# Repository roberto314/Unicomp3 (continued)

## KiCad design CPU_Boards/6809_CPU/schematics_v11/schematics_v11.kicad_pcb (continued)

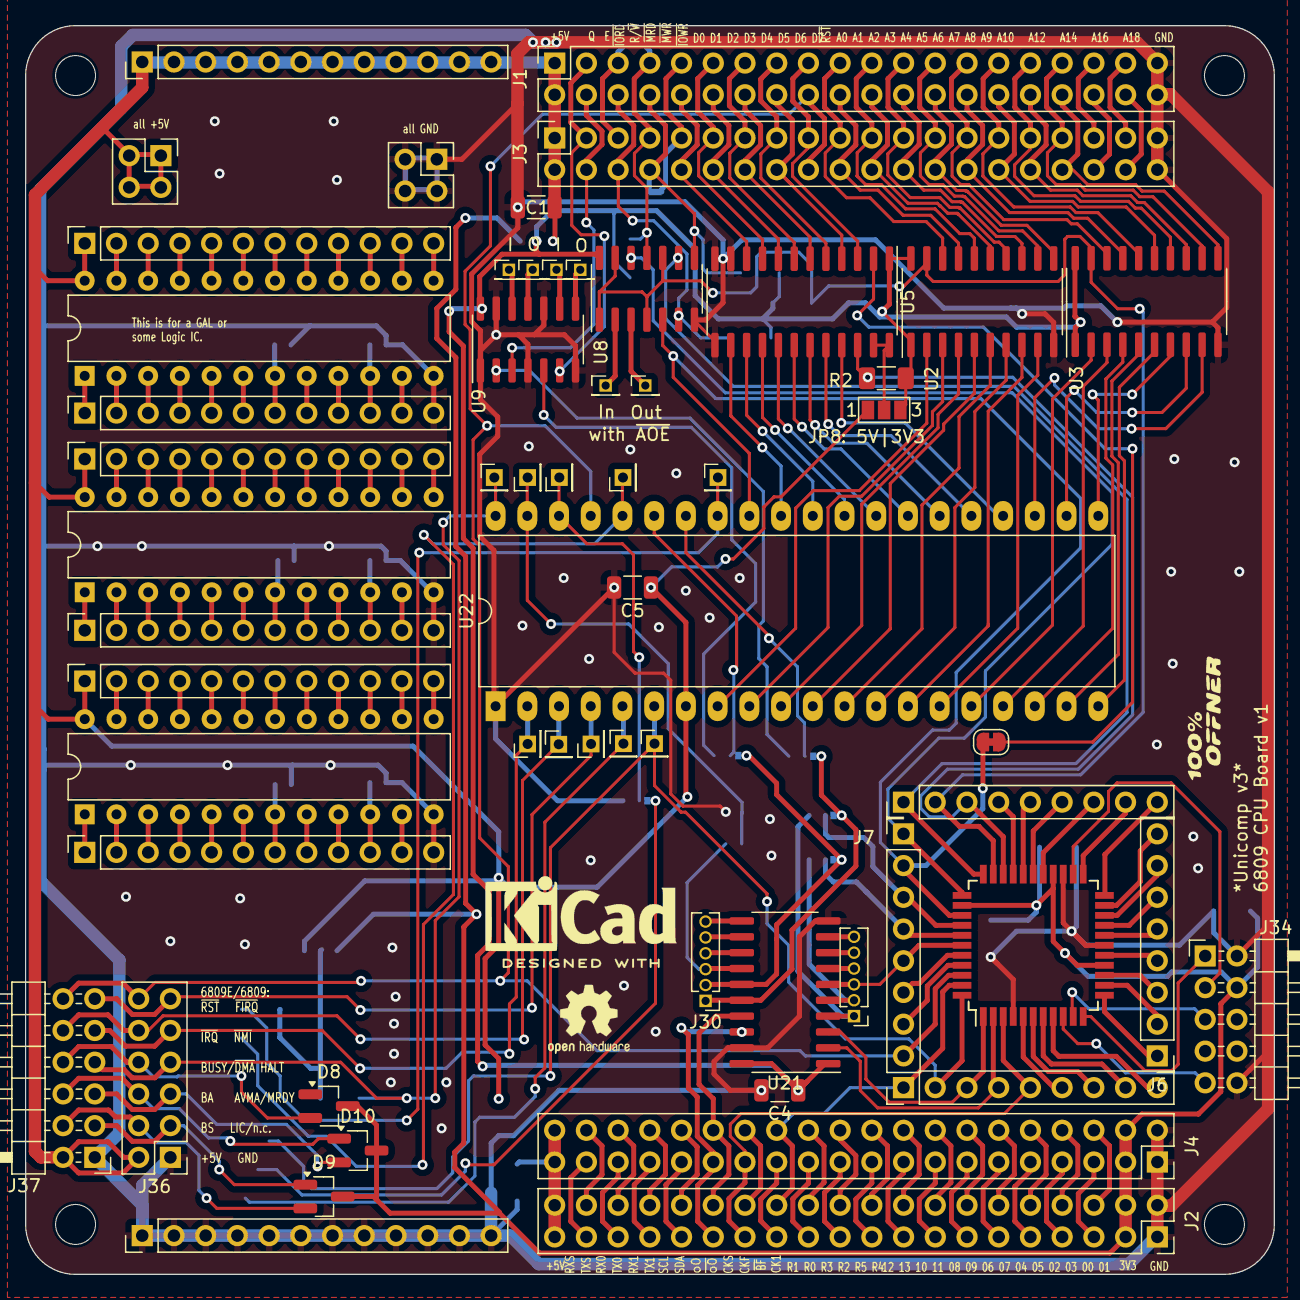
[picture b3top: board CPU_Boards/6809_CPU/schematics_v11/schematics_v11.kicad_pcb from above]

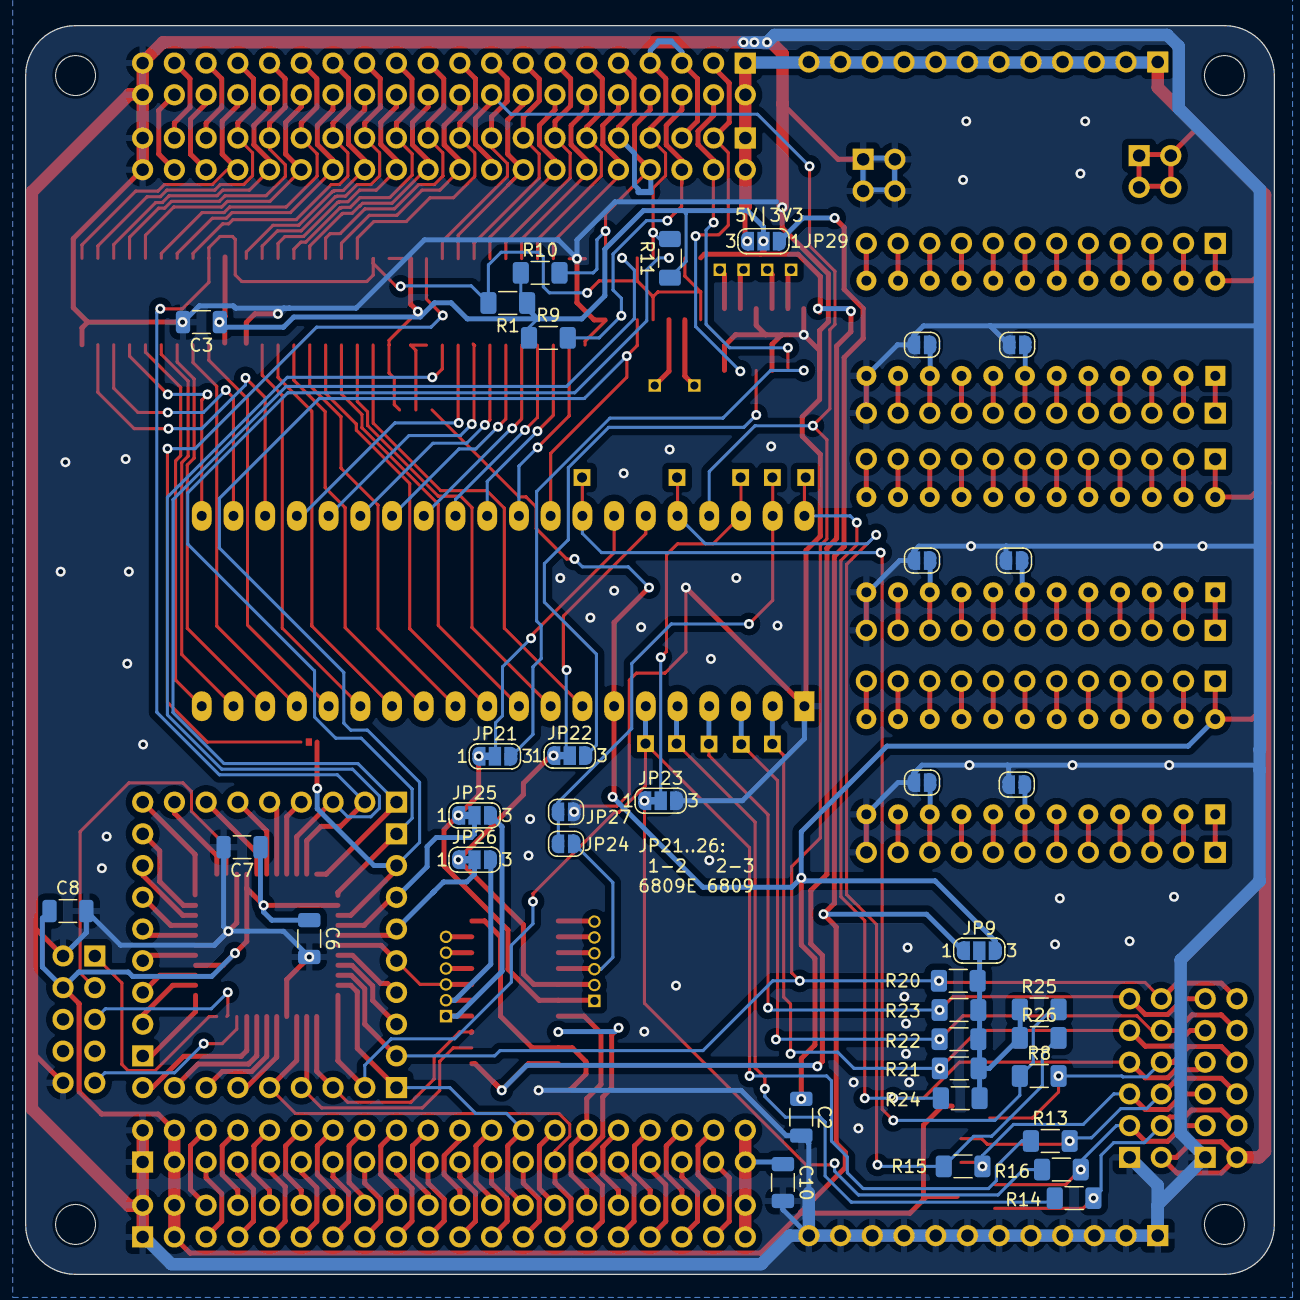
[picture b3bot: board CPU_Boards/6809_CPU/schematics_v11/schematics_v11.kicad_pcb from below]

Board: 2 copper layers, 100.0 x 100.0 mm, 105 parts (39 on the bottom side), 239 nets.

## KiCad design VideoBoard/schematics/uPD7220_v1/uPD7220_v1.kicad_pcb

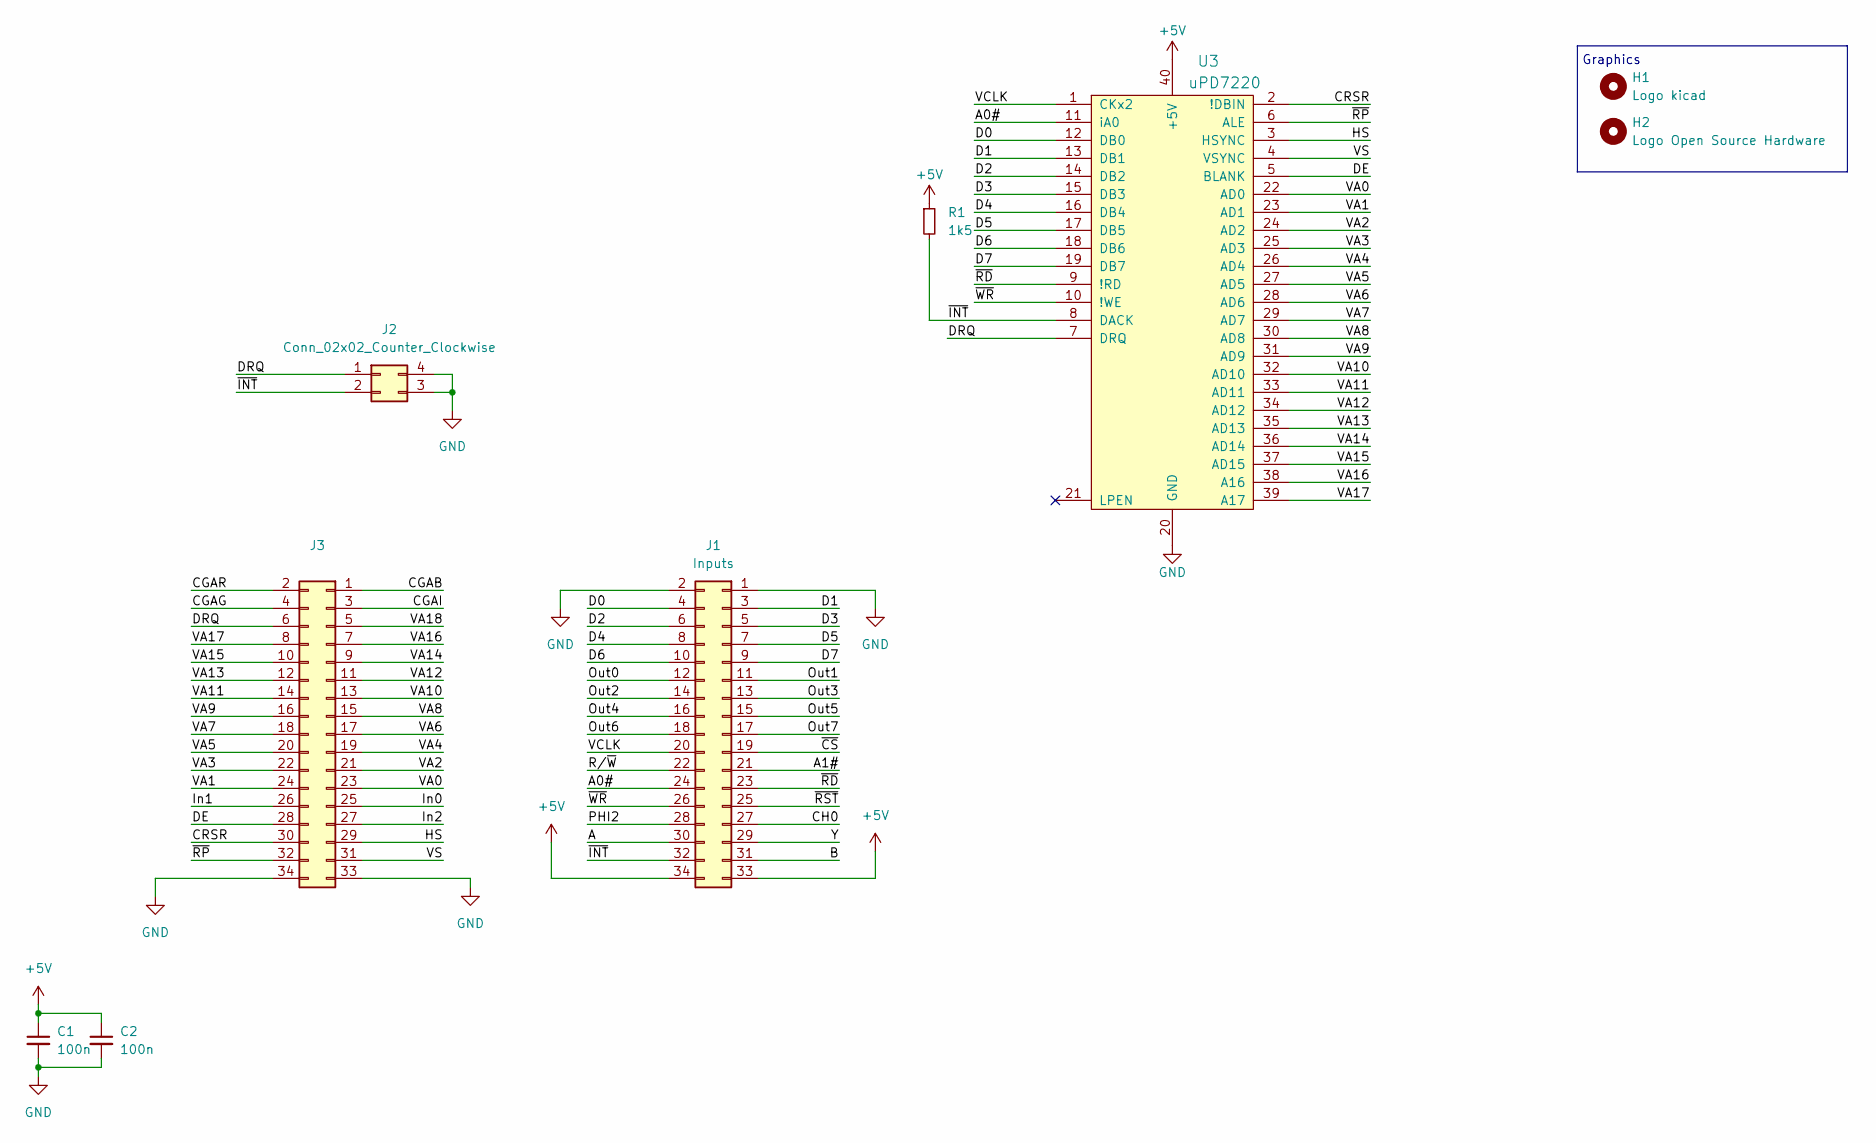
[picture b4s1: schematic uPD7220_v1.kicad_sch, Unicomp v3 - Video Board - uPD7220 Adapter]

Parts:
C1, C2: 100n; C_1206_3216Metric_Pad1.33x1.80mm_HandSolder
H1: Logo kicad; KiCad-Logo2_6mm_SilkScreen
H2: Logo Open Source Hardware; OSHW-Logo2_7.3x6mm_SilkScreen
J1: Inputs; PinHeader_2x17_P2.54mm_Vertical
J2: Conn_02x02_Counter_Clockwise; PinHeader_2x02_P2.54mm_Horizontal
J3: Outputs; PinHeader_2x17_P2.54mm_Vertical
R1: 1k5; R_1206_3216Metric_Pad1.30x1.75mm_HandSolder
U3: uPD7220; DIP-40_W15.24mm_Socket

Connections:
+5V: C1.1, C2.1, J1.33, J1.34, R1.1, U3.40 (+5V)
/A: J1.30
/A0#: J1.24, U3.11 (iA0)
/A1#: J1.21
/B: J1.31
/CGAB: J3.1
/CGAG: J3.4
/CGAI: J3.3
/CGAR: J3.2
/CH0: J1.27
/CRSR: J3.30, U3.2 (!DBIN)
/D0: J1.4, U3.12 (DB0)
/D1: J1.3, U3.13 (DB1)
/D2: J1.6, U3.14 (DB2)
/D3: J1.5, U3.15 (DB3)
/D4: J1.8, U3.16 (DB4)
/D5: J1.7, U3.17 (DB5)
/D6: J1.10, U3.18 (DB6)
/D7: J1.9, U3.19 (DB7)
/DE: J3.28, U3.5 (BLANK)
/DRQ: J2.1, J3.6, U3.7 (DRQ)
/HS: J3.29, U3.3 (HSYNC)
/In0: J3.25
/In1: J3.26
/In2: J3.27
/Out0: J1.12
/Out1: J1.11
/Out2: J1.14
/Out3: J1.13
/Out4: J1.16
/Out5: J1.15
/Out6: J1.18
/Out7: J1.17
/PHI2: J1.28
/R/~W: J1.22
/VA0: J3.23, U3.22 (AD0)
/VA1: J3.24, U3.23 (AD1)
/VA2: J3.21, U3.24 (AD2)
/VA3: J3.22, U3.25 (AD3)
/VA4: J3.19, U3.26 (AD4)
/VA5: J3.20, U3.27 (AD5)
/VA6: J3.17, U3.28 (AD6)
/VA7: J3.18, U3.29 (AD7)
/VA8: J3.15, U3.30 (AD8)
/VA9: J3.16, U3.31 (AD9)
/VA10: J3.13, U3.32 (AD10)
/VA11: J3.14, U3.33 (AD11)
/VA12: J3.11, U3.34 (AD12)
/VA13: J3.12, U3.35 (AD13)
/VA14: J3.9, U3.36 (AD14)
/VA15: J3.10, U3.37 (AD15)
/VA16: J3.7, U3.38 (A16)
/VA17: J3.8, U3.39 (A17)
/VA18: J3.5
/VCLK: J1.20, U3.1 (CKx2)
/VS: J3.31, U3.4 (VSYNC)
/Y: J1.29
/~CS: J1.19
/~INT: J1.32, J2.2, R1.2, U3.8 (DACK)
/~RD: J1.23, U3.9 (!RD)
/~RP: J3.32, U3.6 (ALE)
/~RST: J1.25
/~WR: J1.26, U3.10 (!WE)
GND: C1.2, C2.2, J1.1, J1.2, J2.3, J2.4, J3.33, J3.34, U3.20 (GND)

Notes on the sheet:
Graphics

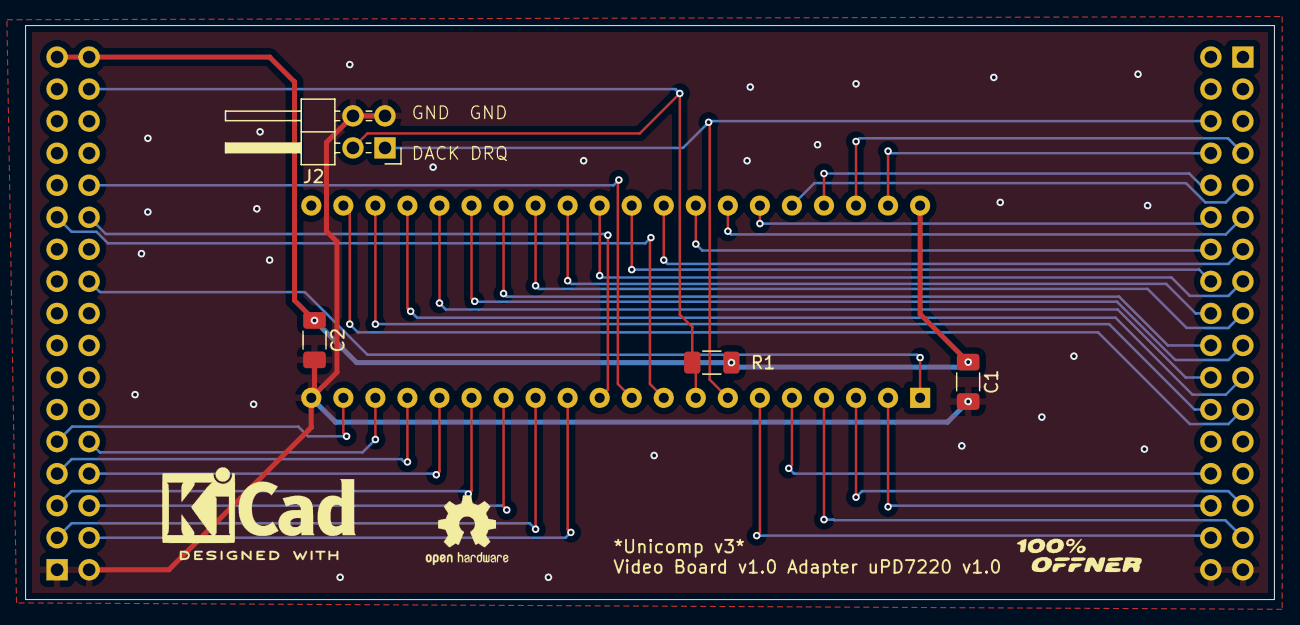
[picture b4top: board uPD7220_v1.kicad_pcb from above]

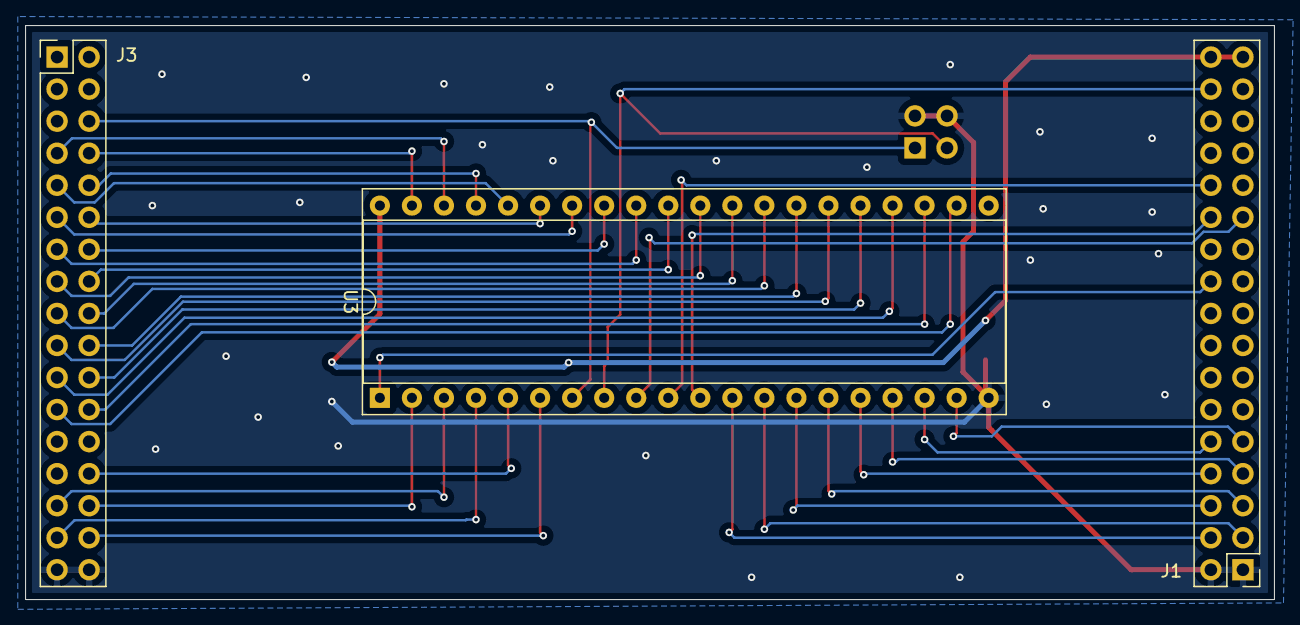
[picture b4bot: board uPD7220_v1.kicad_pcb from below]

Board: 2 copper layers, 99.0 x 45.5 mm, 9 parts (3 on the bottom side), 39 nets.

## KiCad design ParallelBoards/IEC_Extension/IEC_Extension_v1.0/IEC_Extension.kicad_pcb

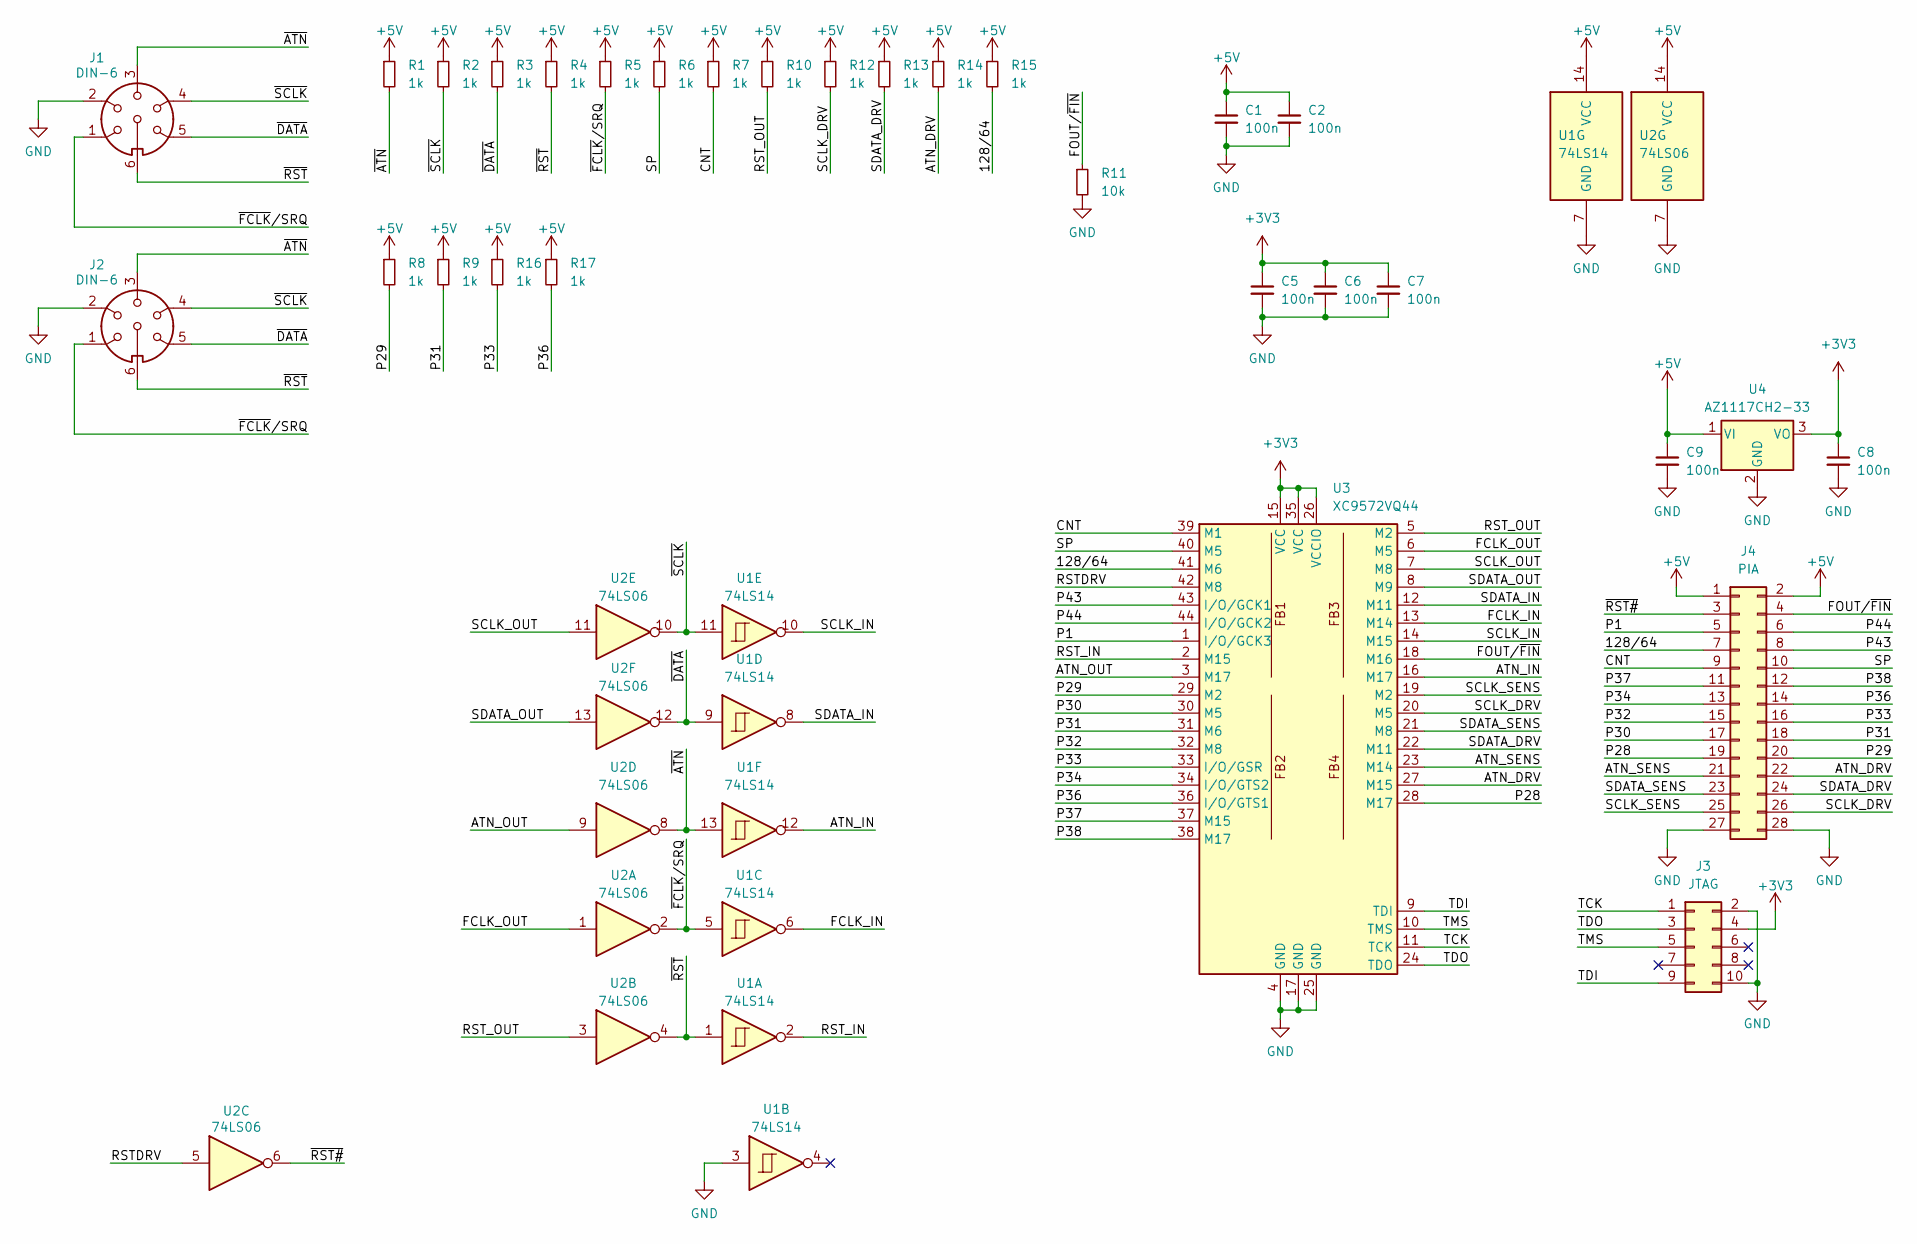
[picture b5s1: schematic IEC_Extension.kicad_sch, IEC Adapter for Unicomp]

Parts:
C1, C2, C5, C6, C7, C8, C9: 100n; C_1206_3216Metric_Pad1.33x1.80mm_HandSolder
J1, J2: DIN-6; C64_IEC
J3: JTAG; PinHeader_2x05_P2.54mm_Horizontal
J4: PIA; PinHeader_2x14_P2.54mm_Vertical
R1, R2, R3, R4, R5, R6, R7, R8, R9, R10, R12, R13, R14, R15, R16, R17: 1k; R_1206_3216Metric_Pad1.30x1.75mm_HandSolder
R11: 10k; R_1206_3216Metric_Pad1.30x1.75mm_HandSolder
U1: 74LS14; SOIC-14_3.9x8.7mm_P1.27mm
U2: 74LS06; SOIC-14_3.9x8.7mm_P1.27mm
U3: XC9572VQ44; TQFP-44_10x10mm_P0.8mm
U4: AZ1117CH2-33; SOT-223-3_TabPin2

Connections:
+3V3: C5.1, C6.1, C7.1, C8.1, J3.4, U3.15 (VCC), U3.26 (VCCIO), U3.35 (VCC), U4.3 (VO)
+5V: C1.1, C2.1, C9.1, J4.1, J4.2, R1.1, R2.1, R3.1, R4.1, R5.1, R6.1, R7.1, R8.1, R9.1, R10.1, R12.1, R13.1, R14.1, R15.1, R16.1, R17.1, U1.14 (VCC), U2.14 (VCC), U4.1 (VI)
/128/64: J4.7, R15.2, U3.41 (M6)
/ATN_DRV: J4.22, R14.2, U3.27 (M15)
/ATN_IN: U1.12, U3.16 (M17)
/ATN_OUT: U2.9, U3.3 (M17)
/ATN_SENS: J4.21, U3.23 (M14)
/CNT: J4.9, R7.2, U3.39 (M1)
/FCLK_IN: U1.6, U3.13 (M14)
/FCLK_OUT: U2.1, U3.6 (M5)
/FOUT/~FIN: J4.4, R11.1, U3.18 (M16)
/P1: J4.5, U3.1 (I/O/GCK3)
/P28: J4.19, U3.28 (M17)
/P29: J4.20, R8.2, U3.29 (M2)
/P30: J4.17, U3.30 (M5)
/P31: J4.18, R9.2, U3.31 (M6)
/P32: J4.15, U3.32 (M8)
/P33: J4.16, R16.2, U3.33 (I/O/GSR)
/P34: J4.13, U3.34 (I/O/GTS2)
/P36: J4.14, R17.2, U3.36 (I/O/GTS1)
/P37: J4.11, U3.37 (M15)
/P38: J4.12, U3.38 (M17)
/P43: J4.8, U3.43 (I/O/GCK1)
/P44: J4.6, U3.44 (I/O/GCK2)
/RSTDRV: U2.5, U3.42 (M8)
/RST_IN: U1.2, U3.2 (M15)
/RST_OUT: R10.2, U2.3, U3.5 (M2)
/SCLK_DRV: J4.26, R12.2, U3.20 (M5)
/SCLK_IN: U1.10, U3.14 (M15)
/SCLK_OUT: U2.11, U3.7 (M8)
/SCLK_SENS: J4.25, U3.19 (M2)
/SDATA_DRV: J4.24, R13.2, U3.22 (M11)
/SDATA_IN: U1.8, U3.12 (M11)
/SDATA_OUT: U2.13, U3.8 (M9)
/SDATA_SENS: J4.23, U3.21 (M8)
/SP: J4.10, R6.2, U3.40 (M5)
/TCK: J3.1, U3.11 (TCK)
/TDI: J3.9, U3.9 (TDI)
/TDO: J3.3, U3.24 (TDO)
/TMS: J3.5, U3.10 (TMS)
/~ATN: J1.3, J2.3, R1.2, U1.13, U2.8
/~DATA: J1.5, J2.5, R3.2, U1.9, U2.12
/~FCLK/SRQ: J1.1, J2.1, R5.2, U1.5, U2.2
/~RST#: J4.3, U2.6
/~RST: J1.6, J2.6, R4.2, U1.1, U2.4
/~SCLK: J1.4, J2.4, R2.2, U1.11, U2.10
GND: C1.2, C2.2, C5.2, C6.2, C7.2, C8.2, C9.2, J1.2, J2.2, J3.2, J3.10, J4.27, J4.28, R11.2, U1.3, U1.7 (GND), U2.7 (GND), U3.4 (GND), U3.17 (GND), U3.25 (GND), U4.2 (GND)

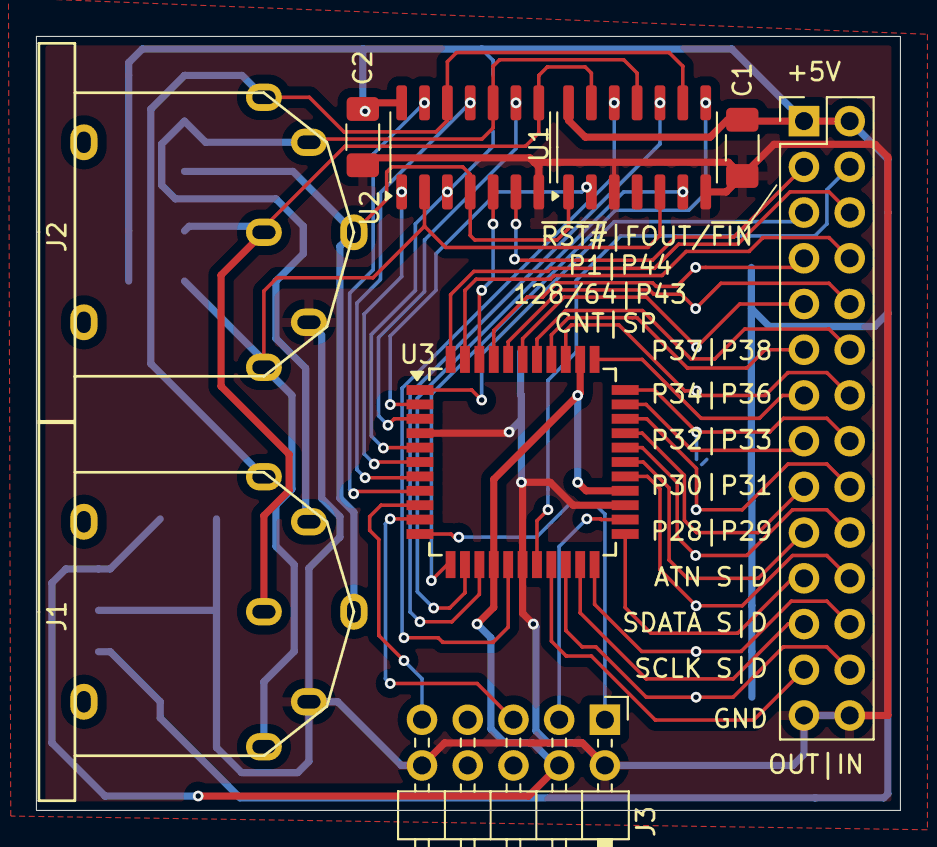
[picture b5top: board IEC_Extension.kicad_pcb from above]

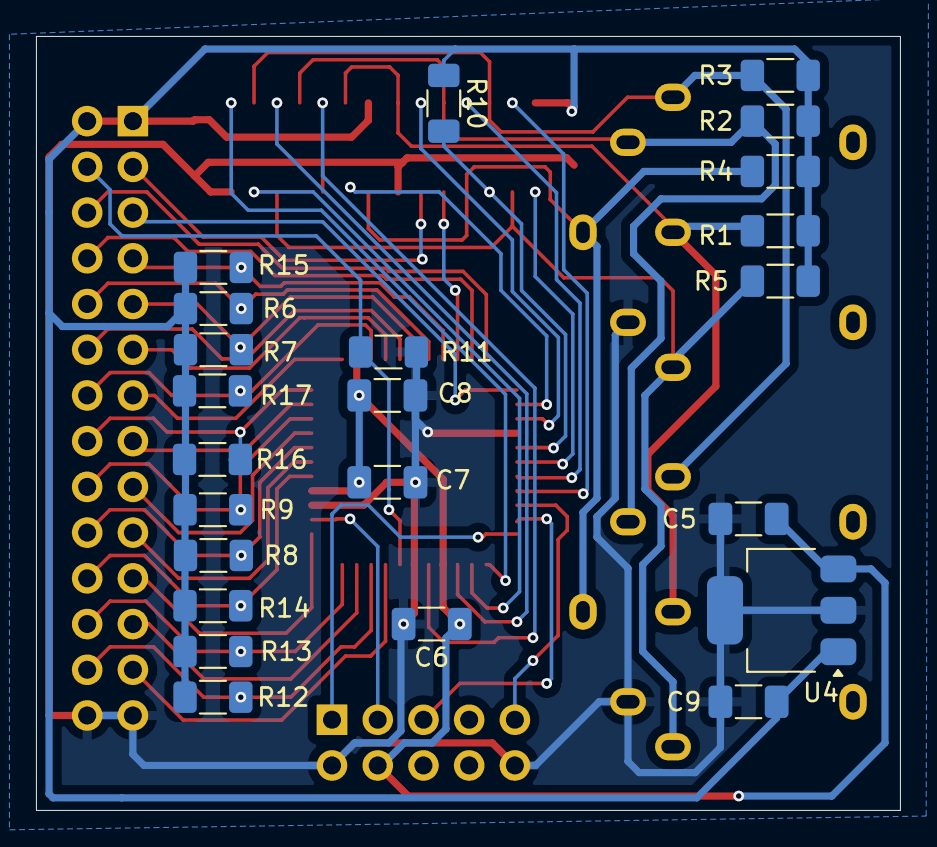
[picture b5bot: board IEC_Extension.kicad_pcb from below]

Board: 2 copper layers, 48.0 x 43.0 mm, 32 parts (23 on the bottom side), 47 nets.

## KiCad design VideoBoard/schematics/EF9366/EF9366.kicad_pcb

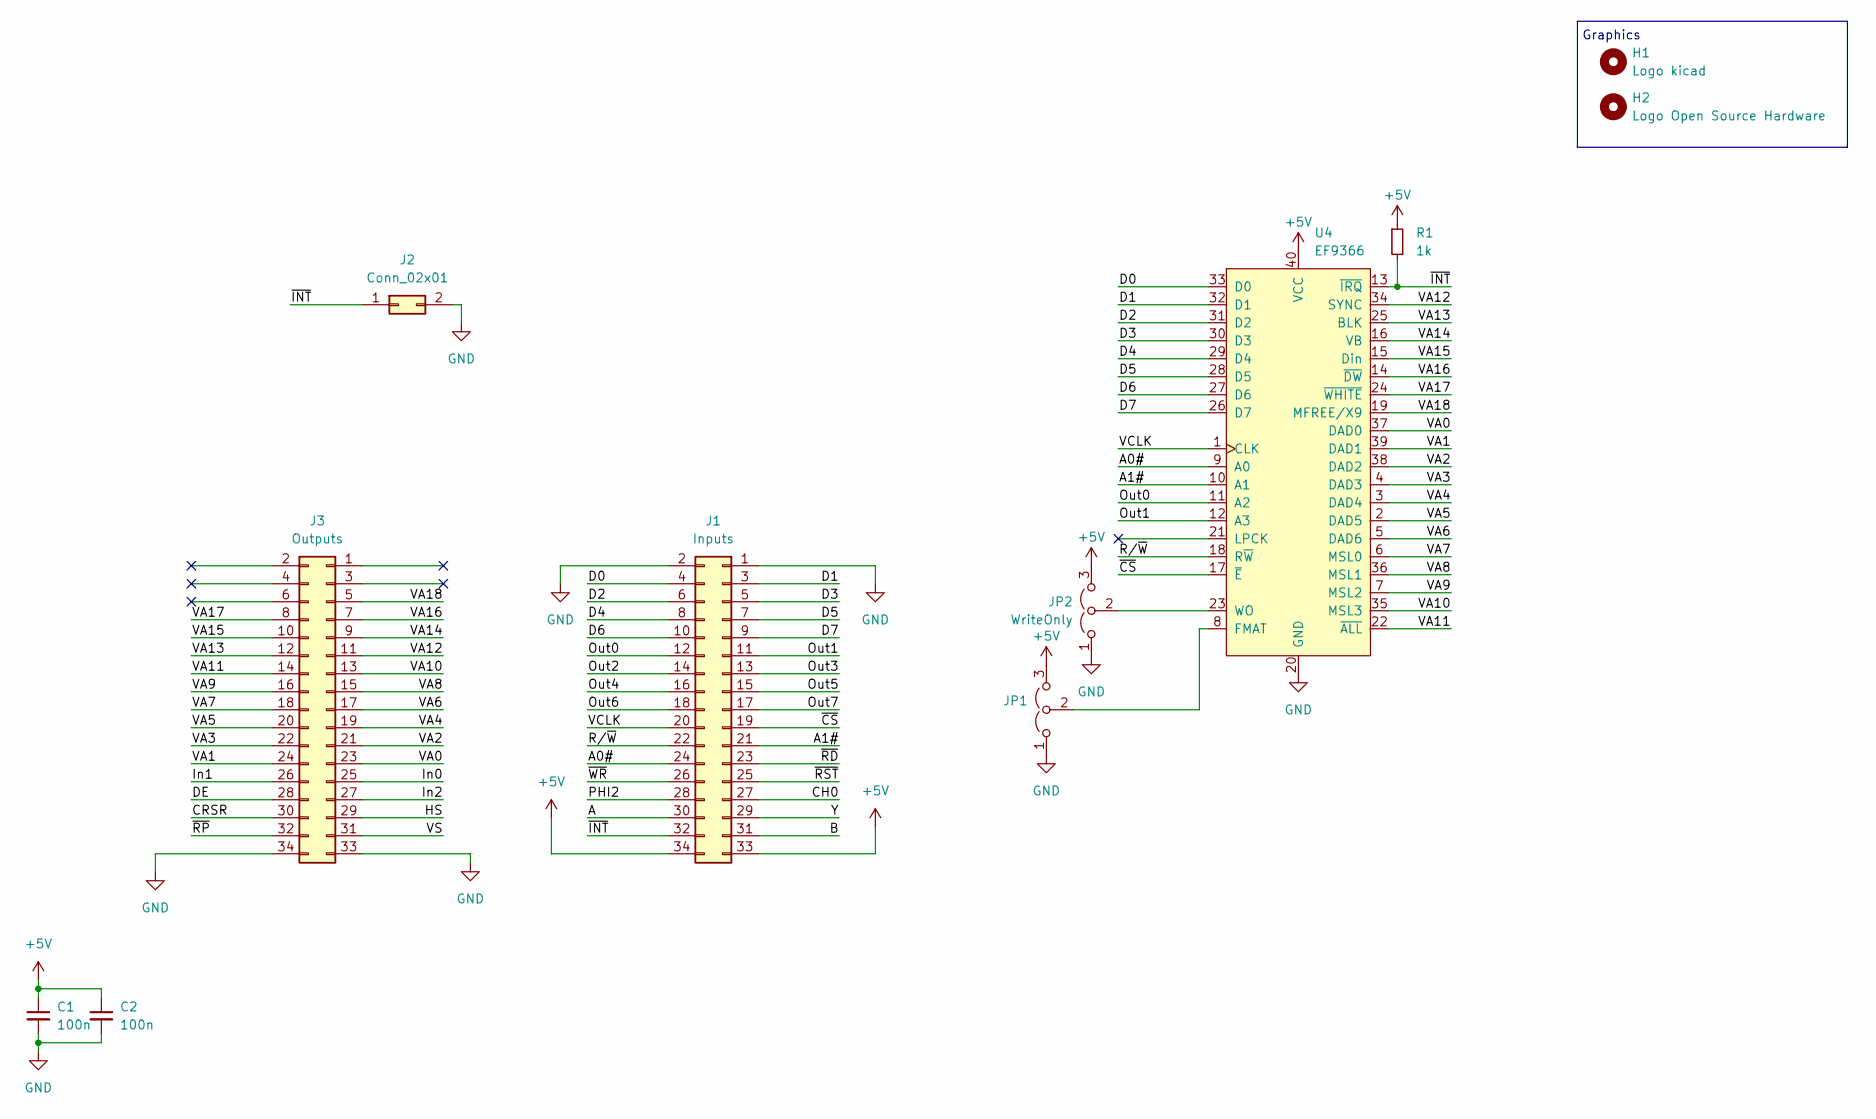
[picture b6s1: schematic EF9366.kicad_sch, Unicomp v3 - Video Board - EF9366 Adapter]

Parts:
C1, C2: 100n; C_1206_3216Metric_Pad1.33x1.80mm_HandSolder
H1: Logo kicad; KiCad-Logo2_6mm_SilkScreen
H2: Logo Open Source Hardware; OSHW-Logo2_7.3x6mm_SilkScreen
J1: Inputs; PinHeader_2x17_P2.54mm_Vertical
J2: Conn_02x01; PinHeader_1x02_P2.54mm_Horizontal
J3: Outputs; PinHeader_2x17_P2.54mm_Vertical
JP1: Format; PinHeader_1x03_P2.54mm_Vertical
JP2: WriteOnly; PinHeader_1x03_P2.54mm_Vertical
R1: 1k; R_1206_3216Metric_Pad1.30x1.75mm_HandSolder
U4: EF9366; DIP-40_W15.24mm_Socket

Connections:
+5V: C1.1, C2.1, J1.33, J1.34, JP1.3 (B), JP2.3 (B), R1.1, U4.40 (VCC)
/A: J1.30
/A0#: J1.24, U4.9 (A0)
/A1#: J1.21, U4.10 (A1)
/B: J1.31
/CH0: J1.27
/CRSR: J3.30
/D0: J1.4, U4.33 (D0)
/D1: J1.3, U4.32 (D1)
/D2: J1.6, U4.31 (D2)
/D3: J1.5, U4.30 (D3)
/D4: J1.8, U4.29 (D4)
/D5: J1.7, U4.28 (D5)
/D6: J1.10, U4.27 (D6)
/D7: J1.9, U4.26 (D7)
/DE: J3.28
/HS: J3.29
/In0: J3.25
/In1: J3.26
/In2: J3.27
/Out0: J1.12, U4.11 (A2)
/Out1: J1.11, U4.12 (A3)
/Out2: J1.14
/Out3: J1.13
/Out4: J1.16
/Out5: J1.15
/Out6: J1.18
/Out7: J1.17
/PHI2: J1.28
/R/~W: J1.22, U4.18 (R~W)
/VA0: J3.23, U4.37 (DAD0)
/VA1: J3.24, U4.39 (DAD1)
/VA2: J3.21, U4.38 (DAD2)
/VA3: J3.22, U4.4 (DAD3)
/VA4: J3.19, U4.3 (DAD4)
/VA5: J3.20, U4.2 (DAD5)
/VA6: J3.17, U4.5 (DAD6)
/VA7: J3.18, U4.6 (MSL0)
/VA8: J3.15, U4.36 (MSL1)
/VA9: J3.16, U4.7 (MSL2)
/VA10: J3.13, U4.35 (MSL3)
/VA11: J3.14, U4.22 (~ALL)
/VA12: J3.11, U4.34 (SYNC)
/VA13: J3.12, U4.25 (BLK)
/VA14: J3.9, U4.16 (VB)
/VA15: J3.10, U4.15 (Din)
/VA16: J3.7, U4.14 (~DW)
/VA17: J3.8, U4.24 (~WHITE)
/VA18: J3.5, U4.19 (MFREE/X9)
/VCLK: J1.20, U4.1 (CLK)
/VS: J3.31
/Y: J1.29
/~CS: J1.19, U4.17 (~E)
/~INT: J1.32, J2.1, R1.2, U4.13 (~IRQ)
/~RD: J1.23
/~RP: J3.32
/~RST: J1.25
/~WR: J1.26
GND: C1.2, C2.2, J1.1, J1.2, J2.2, J3.33, J3.34, JP1.1 (A), JP2.1 (A), U4.20 (GND)
unnamed: JP1.2 (C), U4.8 (FMAT)
unnamed: JP2.2 (C), U4.23 (WO)

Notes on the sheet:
Graphics

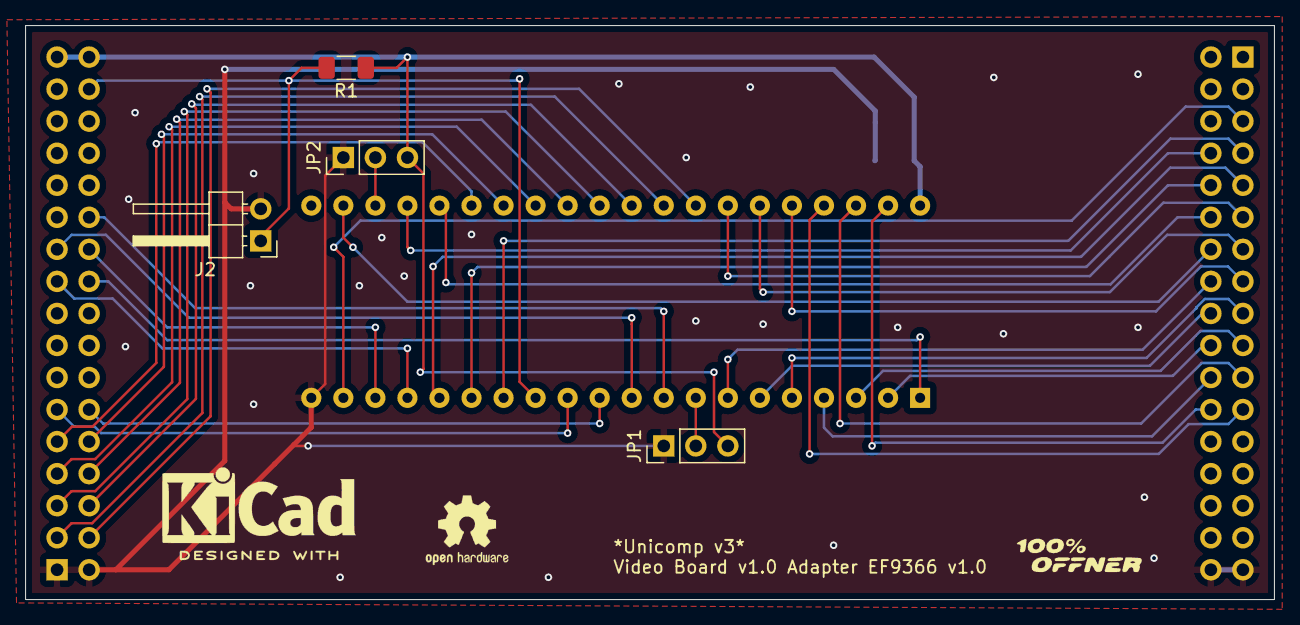
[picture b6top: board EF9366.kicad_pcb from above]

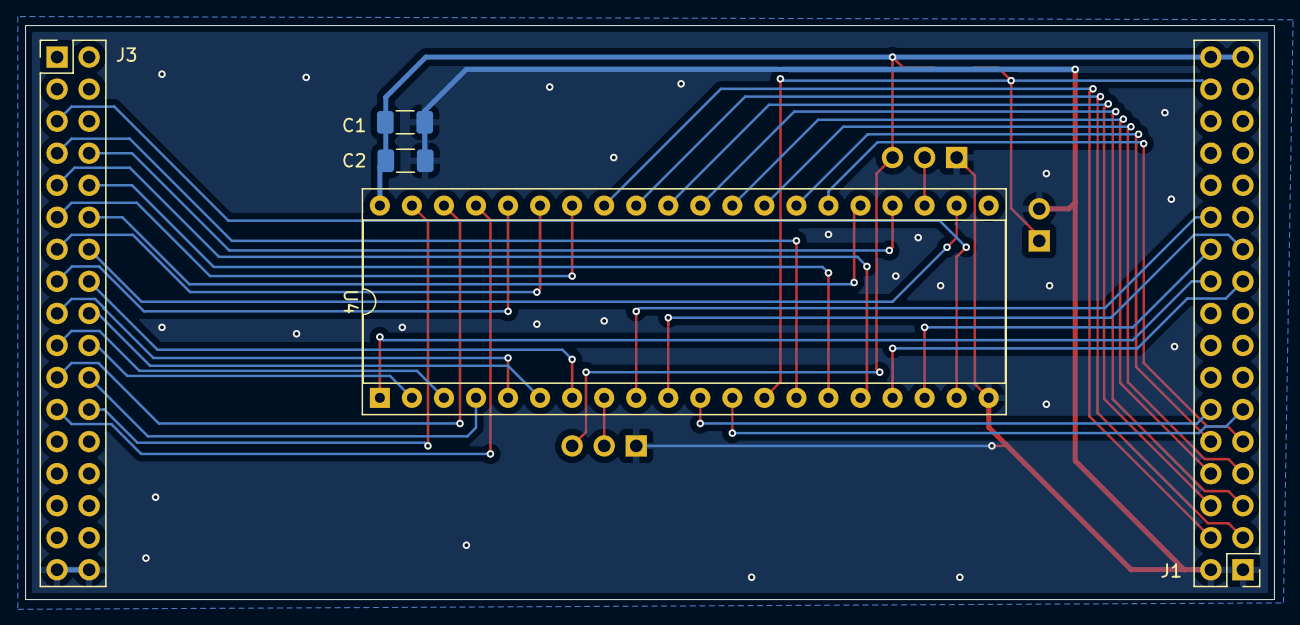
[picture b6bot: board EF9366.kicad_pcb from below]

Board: 2 copper layers, 99.0 x 45.5 mm, 11 parts (5 on the bottom side), 39 nets.
